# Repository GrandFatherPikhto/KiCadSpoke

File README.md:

# KiCadStamp v1.8.0

**KiCadStamp** is a command‑line **PCB cloning and layout automation** tool for **KiCad 10**, designed as an advanced script‑based alternative to the traditional **KiCad Replicate Layout** plugin. It enables automated **block replication**, component placement, and routing of complex multi‑channel designs using **templates**, **roles**, and the IPC API.

- Moving components (capacitors, resistors, ferrites, crystals, etc.) to specified positions.
- Creating vias and **tracks** attached to the spoke as a whole or to individual components.
- **Cloning** repetitive functional blocks (PI‑filters, DAC channels, power supplies) at different board locations.
- Automatic component selection by **roles** and **nets** – no explicit refdes needed.
- Idempotency: repeated runs never duplicate already‑correctly‑placed items.
- Undo of the last operation.
- Extracting templates from the current selection with net parametrisation and custom origin selection.
- Snapshotting hierarchical channels via a file‑based cloner (`clone-extract`).

---

## Key Features

**An advanced, script‑driven alternative to the classic KiCad Replicate Layout plugin**, built for multi‑channel projects and automated design reuse via the KiCad IPC API.

- **Template‑based approach** – geometry is defined once in local coordinates and reused with arbitrary rotation/translation.
- **Automatic component selection** – roles (`LIGHT`, `HEAVY`, `PI_FILTER_C1`, etc.) replace refdes; components are picked from a pool by net and the `Role` field in the schematic.
- **ClonePlacement** – supports two modes:
  - **by selection** – for one‑off instances (e.g., a single MCU);
  - **by nets** – for repeated blocks, with net name parametrisation via placeholders and `params`. Ambiguity is resolved by physical proximity to the anchor (useful for power filters on common rails). You can also use explicit `refs` as a last resort.
- **Generalised vias and tracks** – all elements (vias, tracks, components) are defined in local coordinates and transformed uniformly (translation, rotation, mirroring).
- **Placement registry** – stores UUIDs of created vias and tracks, ensuring idempotency and automatic cleanup of obsolete entries. Reconciliation is now performed against real elements on the board (via `adapter.get_vias()`/`adapter.get_tracks()`), not only the JSON record, avoiding desynchronisation.
- **Pre‑validation** – checks config before any board modification:
  - existence of templates, pads, and anchor components;
  - component pool sufficiency by roles;
  - uniqueness of clone names and physical anchors (`anchor_ref`, `anchor_role`);
  - correctness of resolved via nets against real board nets;
  - validity of `layer`/`mirror` combinations (mirroring only when layer changes);
  - at most one selection‑based `clone_placement` per run (KiCad allows only one active selection).
- **Diagnostics** – scripts for debugging IPC, geometry, and field reading.
- **File‑based cloner** (`clone-extract`) – parses `.net` and `.kicad_pcb` without IPC, builds a twin map of channels for hierarchical projects.
- **Tracks in templates** – templates can include straight track segments (polylines are supported as a sequence of segments). Track collisions are not automatically checked (rely on KiCad DRC).
- **External template files** – templates can be stored separately as JSON or YAML (wrapped in a `cells:` key) and listed under `include:` in the main config, keeping the main file clean and diff‑friendly.
- **Splitting a profile into subsystem files** – `include:` at the root of a profile merges in one or more other YAML files (each carrying any mix of `extract_profiles`/`clone_placements`/`rules`/`cells`), recursively, with a per‑entry `enabled: false` on the include itself to switch a whole subsystem file off without touching every item inside it (see [docs/config.md](docs/config.md) for merge semantics and duplicate/cycle handling).
- **Scripting API** – `kicadstamp.explore.Board` for ad‑hoc read‑only querying (`board.select(role=..., cluster=..., sheet=..., net=...)`), and `kicadstamp.author` for building `ClonePlacement`/`Rule` in real Python instead of hand‑writing repetitive YAML, either applied directly or dumped back to an `include:`‑ready YAML file (see [docs/python.md](docs/python.md)).

---

## Installation and Dependencies

### Requirements
- Python 3.8 or later.
- KiCad 10.0.4 or later (with IPC API enabled).
- The **kipy** library (Python wrapper for KiCad IPC).

### Installation
```bash
pip install kipy pyyaml sexpdata
```
(For diagnostics, `psutil` may be required.)

### Setting up Roles in the Schematic (Eeschema)
1. Open the symbol in Eeschema.
2. Add a field named **Role** with a value matching the role in the template (e.g., `LIGHT`, `HEAVY`).
3. Run **Update PCB from Schematic** to propagate the field to the board.
4. Verify readability with:
   ```bash
   python -m kicadstamp.diagnostics.test_custom_field C5 --field Role
   ```

---

## Key Concepts

### Why "Spoke"?
In electronics, decoupling/support components (capacitors, pi‑filters) often radiate outward from an
IC's pins, like spokes on a wheel. KiCadStamp automates building this kind of "spoke" topology, letting
you **stamp** it out by rule and role wherever it's needed:
- **Template (`SpokeTemplate`)** – the geometry of one spoke (a capacitor + via + track, or a whole filter block).
- **Spoke (`ManualSpoke`)** – a rule that takes a spoke template and attaches it to a specific pad.
- **Cloning (`ClonePlacement`)** – the next level: takes a template – one spoke or a whole bundle of them
  (e.g. a channel) – and stamps it as an independent unit anywhere on the board, not just on an IC pad.

That maps onto the tool's two names: **Spoke** is the domain shape (the radiating placement pattern),
**Stamp** is the action – the tool that replicates it by rule.

### Template (SpokeTemplate)
A template describes the **local geometry** of one "spoke" – a set of components, vias, and tracks relative to a local origin (0,0) in the `along/across` coordinate system. It contains:
- **`vias`** – vias at the spoke level (usually the power net).
- **`components`** – a list of slots, each with a `role`, local coordinates, angle, and a list of vias (usually to GND).
- **`tracks`** – straight track segments (layer, width, net).

All coordinates are defined **once** at `rotation_deg=0`; when applied, the template is rotated as a whole.

#### Template layer (`layer`)
Each template has an absolute layer (`F.Cu` or `B.Cu`), automatically set during extraction (`extract`). Components on a different layer get an explicit `layer` in their slot.

#### Net parametrisation during extraction
With the `--net-template` option, you can replace literal net names with patterns containing placeholders (e.g., `DAC1_DB1 → DAC{channel}_DB1`) at extraction time. This eliminates manual YAML editing.

### Spoke (ManualSpoke)
Attaches a template to a specific IC pin:
- `pad` – pad number of the target component.
- `shift_x_mm`, `shift_y_mm` – flat shift from the pad centre to the template origin.
- `rotation_deg` – rotation of the entire template.

**Important:** In new config versions, each rule (`rules`) must have its own `anchor_ref`. The global `target_ref` has been removed.

### Roles and Component Pool
Instead of refdes, **roles** are used in the config. For each net (`rule.net`), a pool of components is built, where each component:
- Has a `Role` field with the required value.
- Has at least one pad connected to that net.

Components are sorted in natural numeric order (`C5` < `C10`) and consumed in the order of spokes.

### Cloning (ClonePlacement)
Allows applying a template at an arbitrary point on the board, without tying to IC pads. Supports:
- **Selection mode** – reads roles from the current selection in the PCB editor. You can either omit `nets`/`params` or explicitly set `by_selection: true`. Only one such clone can be processed per run (due to KiCad's single‑selection limitation).
- **Net mode** – for each role, a net is specified (via `nets` or `net_template` with placeholders resolved by `params` and `net_overrides`). If multiple candidates are electrically indistinguishable, the tool can pick the one closest to the anchor (if the distance margin is sufficient). This is useful for power filters on a common rail.
- **Anchor by role** (`anchor_role`) – an alternative to `anchor_ref`: instead of a refdes, you can specify the `Role` field of the anchor component. This survives re‑annotation. You can further narrow the search with `anchor_sheet` (local net prefix) or `anchor_pad`.
- **Explicit refs** (`refs`) – a last‑resort override when candidates are indistinguishable by nets, selection, or proximity.

### Placement Registry (PlacementRegistry + TrackRegistry)
Separate registries for vias and tracks (JSON files next to the config). On subsequent runs:
- already correctly placed items are skipped;
- those that changed position/parameters are deleted and recreated;
- obsolete entries (keys not present in the new plan) are removed (prune).

**Important:** Reconciliation now checks against real elements on the board (`adapter.get_vias()`/`adapter.get_tracks()`), not only the JSON record, preventing desynchronisation due to manual deletions or crashes between registry write and board commit.

### Net Resolution (`net_resolution`)
For cloned templates, net names go through a three‑step resolution:
1. **Literal** – if no placeholders.
2. **Placeholder** – substitution from `params` (e.g., `{channel}` → `2`).
3. **net_overrides** – final override of the resolved name (for hierarchical paths).

During extraction, the reverse operation (`--net-template`) is available, turning literals into patterns.

---

## Configuration File Format (YAML)

Full field-by-field reference for every section (`cells`/`rules`/`clone_placements`/
`thermal_via_arrays`/`points`/`include`/`extract_profiles`) with real, currently-loading examples now
lives in its own page: [docs/config.md](docs/config.md).

---

## CLI Commands

All commands are run via `kicadstamp_cli.py`. If the subcommand is omitted, `apply` is assumed.

### `apply` – apply placement

```bash
python kicadstamp_cli.py apply config.yaml [options]
```

Options:
- `--dry-run` – only show the plan, do not apply changes.
- `--timeout-ms` – IPC timeout in ms (default 20000).
- `--batch-size` – batch size for commits (default 10).
- `--verbose` – verbose output (DEBUG).
- `--log-file` – save logs to a file.
- `--no-collision-check` – disable collision checking.
- `--collision-margin` – margin in mm (default 0.2).
- `--only NAME` – process only the `rules`/`clone_placements`/`thermal_via_arrays` with this name (repeatable); everything else is skipped entirely. `name:` is mandatory on every such entry.

### `extract` – extract template from selection (enhanced)

```bash
python kicadstamp_cli.py extract --name template_name --output config.yaml [--verbose] [--log-file] [--param KEY=VALUE] [--net-template LITERAL=PATTERN] [--origin-by-via-net NET] [--origin-by-component-role ROLE]
```

New options:
- `--param KEY=VALUE` – parameter for `--net-template` verification (e.g., `channel=1`), not written to template.
- `--net-template LITERAL=PATTERN` – replace a real net with a pattern containing placeholders (e.g., `DAC1_DB1=DAC{channel}_DB1`). Can be repeated.
- `--origin-by-via-net NET` – set origin to the position of a via on the specified net (instead of bbox). Fatal if the net is missing or ambiguous.
- `--origin-by-component-role ROLE` – set origin to the position of a component with the specified role.

**Important:** The `--output` extension determines format: `.json` → JSON, otherwise YAML. The file is written wrapped under a `cells:` key, ready to be listed directly under `include:`.

### `undo` – undo the last operation

```bash
python kicadstamp_cli.py undo [--verbose] [--log-file]
```

### `clone-extract` – snapshot a channel (file‑based cloner)

```bash
python kicadstamp_cli.py clone-extract --net project.net --pcb project.kicad_pcb --channel Channel_0 --output snapshot.yaml [--verbose]
```

---

## Usage Examples

### 1. Standard run
```bash
python kicadstamp_cli.py 10CL006YE144C8G.yaml
```

### 2. Dry run
```bash
python kicadstamp_cli.py config.yaml --dry-run
```

### 3. Process a single clone (selection mode)
```bash
python kicadstamp_cli.py config.yaml --only pi_filter_vccio
```

### 4. Extract a template with parametrisation and origin by via
Select the elements on the board, then:
```bash
python kicadstamp_cli.py extract --name my_filter --output my_filter.json --net-template "DAC1_DB1=DAC{channel}_DB1" --param channel=1 --origin-by-via-net "/Channel_0/DAC/+3V3_CLKVDD" --verbose
```

### 5. Undo
```bash
python kicadstamp_cli.py undo --verbose
```

---

## Diagnostics and Known Issues

### KiCad Bug #24966 (crash on first write via IPC)
When the Schematic Editor is open, the session's first `begin_commit()`/`push_commit()` transaction (even a
no-op one) can crash KiCad (null pointer in `API_HANDLER_EDITOR::checkForBusy`).

**Symptoms:** KiCad silently closes, client gets `ConnectionError: Error receiving reply from KiCad: Timed out`.

**Workaround:** close the schematic editor before running `apply`. The tool includes a warning and retries,
but the crash remains a KiCad defect. In practice it's specifically the *session's first* write that's
vulnerable — if the first `apply` run is done with only the PCB Editor open, opening the Schematic Editor
afterwards is usually safe. Full write-up, a related bug (#24970), and the full crash-hunting toolkit —
see [docs/crash_hunting.md](./docs/crash_hunting.md).

### Diagnostic scripts
`kicadstamp/diagnostics/` includes:
- `diagnose_first_write_crash.py` – reproduces the crash ladder, see [docs/diagnose_first_write_crash.md](./docs/diagnose_first_write_crash.md).
- `test_custom_fields.py` – checks `Role` field reading.
- `test_move_one_cap.py`, `test_flip_one_cap.py`, `test_create_one_via.py`, `test_pad_mirror_convention.py`, `get_selected_component.py`, `get_pad_bbox.py`, `diagnostic_keepout.py`.

---

## Project Structure (brief)

```
kicadstamp/
├── __init__.py
├── kicadstamp_cli.py          # CLI entry point
├── apply_pipeline.py          # cmd_apply and ApplyPipeline class
├── cli_extract.py             # cmd_extract command logic
├── logging_setup.py           # Logging configuration
├── runtime_context.py         # RuntimeContext dataclass
├── sheet_names.py             # Sheet UUID → name resolution
├── i18n.py                    # gettext internationalisation
├── author.py                  # Scripting: dump/apply helpers (explore/author)
├── explore.py                 # Board query helpers
├── config/                    # Configuration package (loader.py, models.py, includes.py)
├── constants.py               # Global constants (ROLE_FIELD_NAME, tolerances, etc.)
├── exceptions.py              # Exception hierarchy
├── validation.py              # Pre‑checks (nets, uniqueness, selection mode, layer/mirror)
├── registry.py                # Via and track registries (reconcile with live elements)
├── net_resolution.py          # Net resolution with placeholders for ClonePlacement
├── template_extraction.py     # Extract with parametrisation and custom origin
├── undo.py                    # Undo last placement operation
├── geometry/                  # Spoke_layout, keepout, thermal_grid, pad_projection, clone_geometry
├── kicad/                     # KiCad IPC adapter and IBoardAdapter interface
├── placement/                 # Planner, executors, services
│   ├── services/              # component_pool, clone_role_resolver, position_tracker, component_resolver, etc.
├── cloner/                    # File‑based cloner (extract, netlist, pcb, models, sexp)
├── diagnostics/               # Diagnostic scripts
├── utils/                     # Utilities
│   └── units.py               # MM = 1_000_000 constant
└── tests/                     # Unit and integration tests
```

---

## 📚 Technical Documentation

Detailed documentation is in the `docs/` folder:

- [Project architecture](./docs/architect.md)
- [CLI commands](./docs/commands.md)
- [Geometry utilities](./docs/geometry.md)
- [KiCad adapter](./docs/kicad.md)
- [Using kipy](./docs/kipy.md)
- [Placement planning and execution](./docs/placement.md)
- [YAML configuration reference](./docs/config.md)
- [Coding placement in Python: explore/author](./docs/python.md)
- [PyQt6 GUI](./docs/gui.md)
- [fieldstool: bulk Role/Cluster set/rename in .kicad_sch](./docs/fieldstool.md)
- [Tests](./docs/tests.md)
- [Top‑level modules](./docs/uplevel_modules.md)
- [File‑based cloner](./docs/cloner.md)
- [Diagnostics](./docs/diagnostics.md)
- [KiCad crash hunting toolkit (#24966 / #24970)](./docs/crash_hunting.md)
- [`diagnose_first_write_crash.py` reference](./docs/diagnose_first_write_crash.md)
- [Internationalization (i18n) — gettext/Babel](./docs/i18n.md)
- [Template rotation and transformation](./docs/rotate_template.md)
- [Module dependency diagram](./docs/diagram.md)

---

## Versioning

Single source of truth: `__version__` in [`kicadstamp/__init__.py`](./kicadstamp/__init__.py) — this README's
header and `kicadstamp_cli.py --version`/`-V` both read it, not a separate literal. Versioned by
session/stage, not by commit: MINOR bumps once per notable block of work (e.g. one architecture‑refactor
session, regardless of how many commits it took), PATCH for point fixes made between stages, MAJOR
reserved for actual breaking changes to the CLI or YAML config format.

---

## License

This project is distributed under the **MIT** license. See the `LICENSE` file for details.

---

**KiCadStamp** is not just a utility – it's a modern alternative to manual block copying in KiCad.

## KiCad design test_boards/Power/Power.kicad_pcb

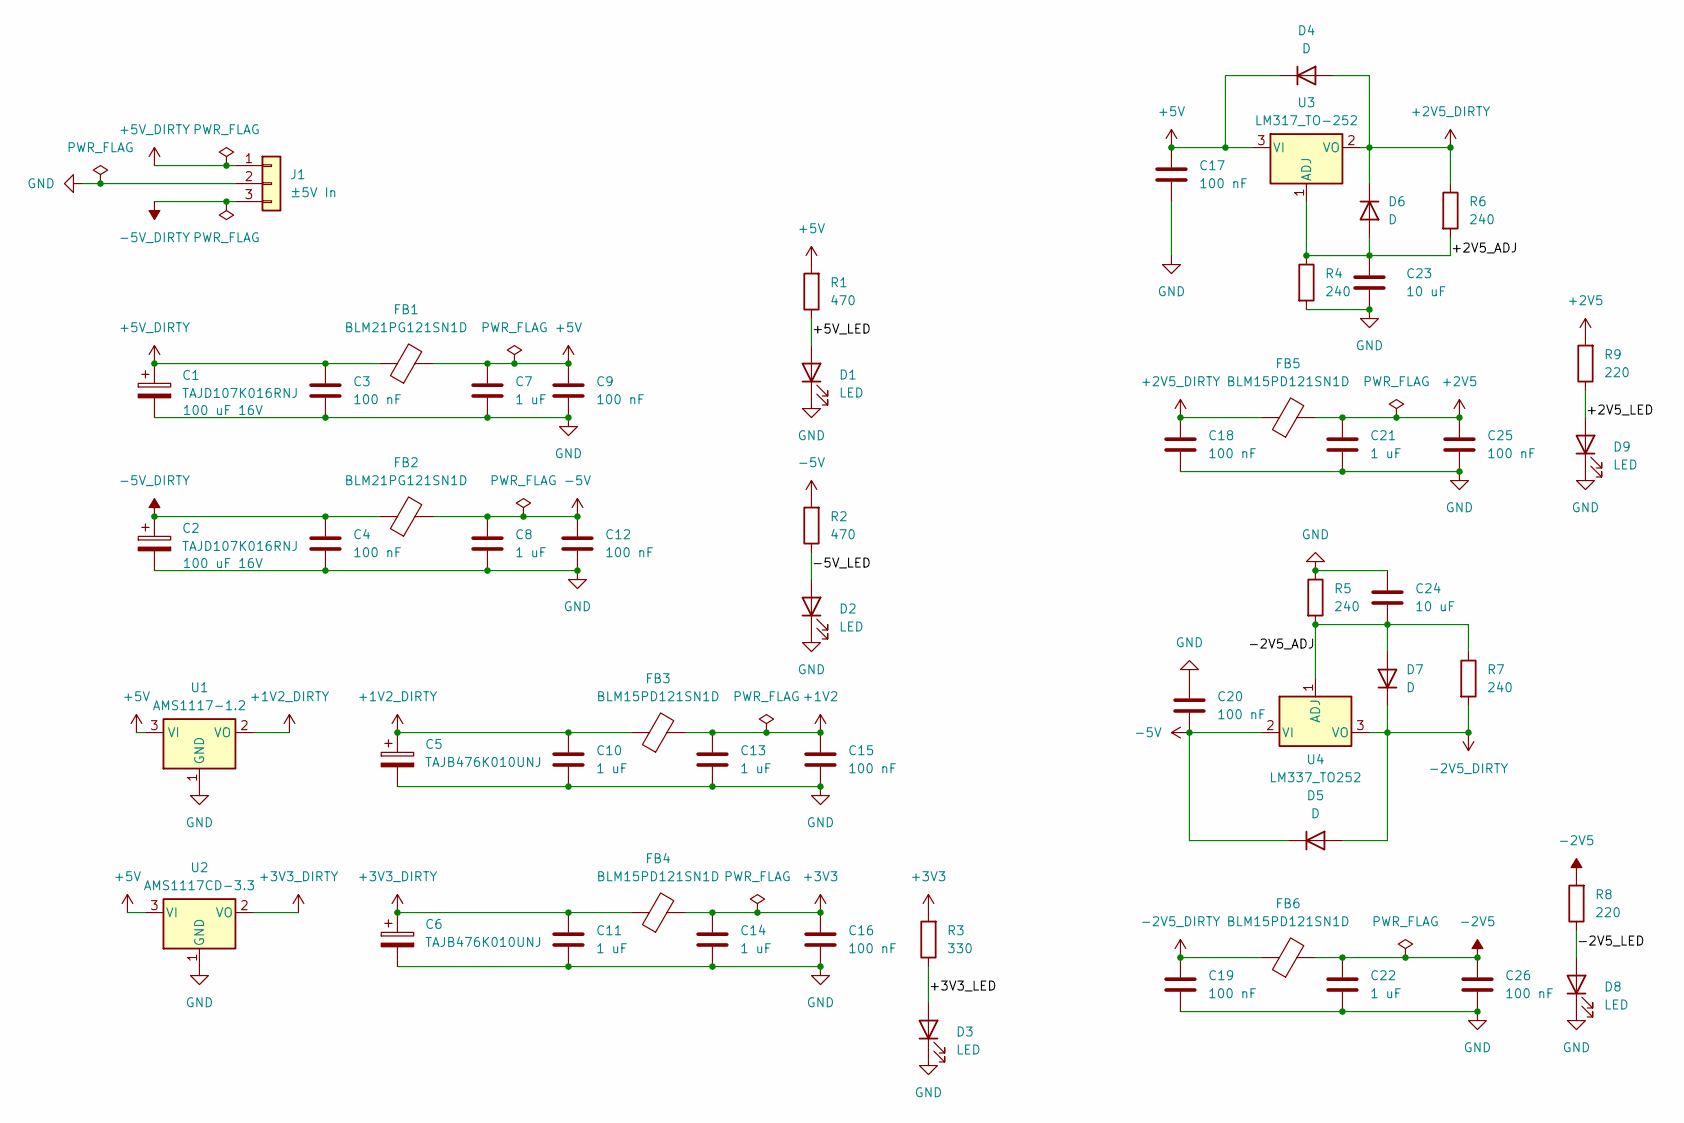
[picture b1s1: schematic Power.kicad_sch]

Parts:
C1, C2: TAJD107K016RNJ; CP_EIA-7343-20_Kemet-V_HandSolder
C3, C4, C9, C12, C15, C16, C17, C18, C19, C20, C25, C26: 100 nF; C_0603_1608Metric_Pad1.08x0.95mm_HandSolder
C5, C6: TAJB476K010UNJ; CP_EIA-3528-12_Kemet-T_HandSolder
C7, C8: 1 uF; C_1206_3216Metric_Pad1.33x1.80mm_HandSolder
C10, C11, C13, C14, C21, C22: 1 uF; C_0603_1608Metric_Pad1.08x0.95mm_HandSolder
C23, C24: 10 uF; C_0805_2012Metric_Pad1.18x1.45mm_HandSolder
D1, D2, D3, D8, D9: LED; D_0805_2012Metric_Pad1.15x1.40mm_HandSolder
D4, D5, D6, D7: D; D_SMA_Handsoldering
FB1, FB2: BLM21PG121SN1D; L_0805_2012Metric
FB3, FB4, FB5, FB6: BLM15PD121SN1D; L_0402_1005Metric
J1: ±5V In; JST_XH_B3B-XH-A_1x03_P2.50mm_Vertical
R1, R2: 470; R_0603_1608Metric_Pad0.98x0.95mm_HandSolder
R3: 330; R_0603_1608Metric_Pad0.98x0.95mm_HandSolder
R4, R5, R6, R7: 240; R_0603_1608Metric_Pad0.98x0.95mm_HandSolder
R8, R9: 220; R_0603_1608Metric_Pad0.98x0.95mm_HandSolder
U1: AMS1117-1.2; SOT-223-3_TabPin2
U2: AMS1117CD-3.3; TO-252-3_TabPin2
U3: LM317_TO-252; TO-252-2
U4: LM337_TO252; TO-252-2

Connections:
+1V2: C13.1, C15.1, FB3.2
+1V2_DIRTY: C5.1, C10.1, FB3.1, U1.2 (VO)
+2V5: C21.1, C25.1, FB5.2, R9.2
+2V5_DIRTY: C18.1, D4.2 (A), D6.1 (K), FB5.1, R6.1, U3.2 (VO)
+3V3: C14.1, C16.1, FB4.2, R3.2
+3V3_DIRTY: C6.1, C11.1, FB4.1, U2.2 (VO)
+5V: C7.1, C9.1, C17.2, D4.1 (K), FB1.2, R1.2, U1.3 (VI), U2.3 (VI), U3.3 (VI)
+5V_DIRTY: C1.1, C3.1, FB1.1, J1.1
-2V5: C22.1, C26.1, FB6.2, R8.2
-2V5_DIRTY: C19.1, D5.2 (A), D7.1 (K), FB6.1, R7.2, U4.3 (VO)
-5V: C8.1, C12.1, C20.1, D5.1 (K), FB2.2, R2.2, U4.2 (VI)
-5V_DIRTY: C2.1, C4.1, FB2.1, J1.3
/+2V5_ADJ: C23.1, D6.2 (A), R4.1, R6.2, U3.1 (ADJ)
/+2V5_LED: D9.2 (A), R9.1
/+3V3_LED: D3.2 (A), R3.1
/+5V_LED: D1.2 (A), R1.1
/-2V5_ADJ: C24.2, D7.2 (A), R5.2, R7.1, U4.1 (ADJ)
/-2V5_LED: D8.2 (A), R8.1
/-5V_LED: D2.2 (A), R2.1
GND: C1.2, C2.2, C3.2, C4.2, C5.2, C6.2, C7.2, C8.2, C9.2, C10.2, C11.2, C12.2, C13.2, C14.2, C15.2, C16.2, C17.1, C18.2, C19.2, C20.2, C21.2, C22.2, C23.2, C24.1, C25.2, C26.2, D1.1 (K), D2.1 (K), D3.1 (K), D8.1 (K), D9.1 (K), J1.2, R4.2, R5.1, U1.1 (GND), U2.1 (GND)

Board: 4 copper layers, 55 parts (0 on the bottom side), 20 nets, no tracks yet.

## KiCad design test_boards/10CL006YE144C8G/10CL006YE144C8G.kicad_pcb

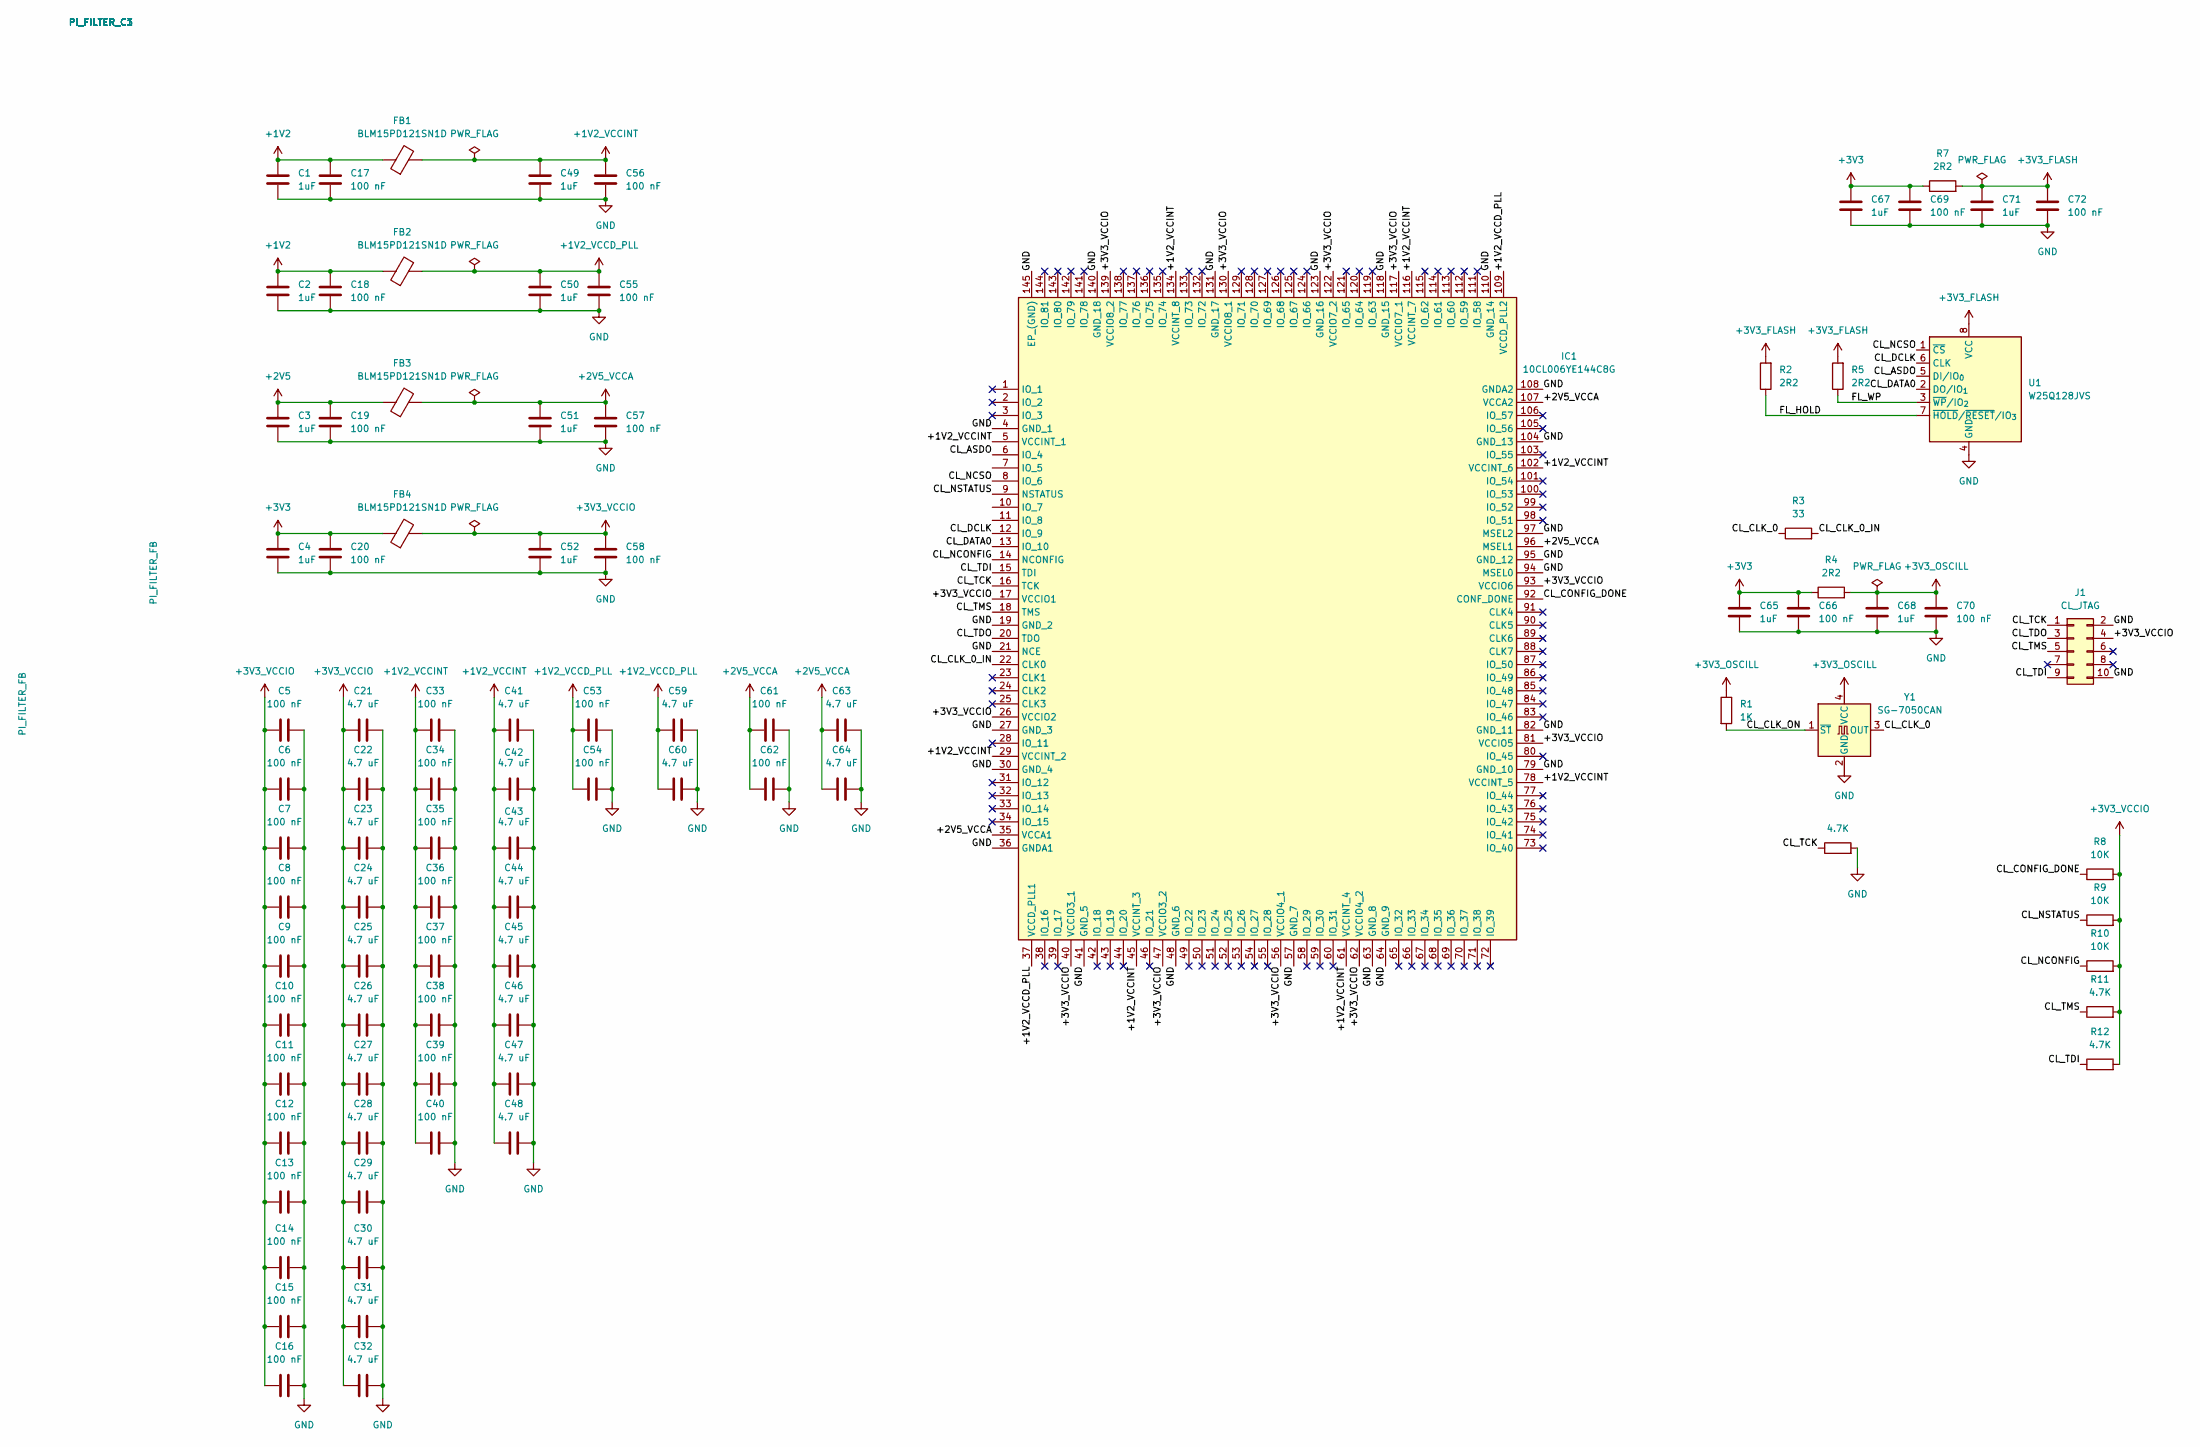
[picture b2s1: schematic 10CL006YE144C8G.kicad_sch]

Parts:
C1, C2, C3, C4, C49, C50, C51, C52, C65, C67, C68, C71: 1uF; C_0603_1608Metric_Pad1.08x0.95mm_HandSolder
C5, C6, C7, C8, C9, C10, C11, C12, C13, C14, C15, C16, C17, C18, C19, C20, C33, C34, C35, C36, C37, C38, C39, C40, C53, C54, C55, C56, C57, C58, C61, C62, C66, C69, C70, C72: 100 nF; C_0402_1005Metric_Pad0.74x0.62mm_HandSolder
C21, C22, C23, C24, C25, C26, C27, C28, C29, C30, C31, C32, C41, C42, C43, C44, C45, C46, C47, C48, C59, C60, C63, C64: 4.7 uF; C_0603_1608Metric_Pad1.08x0.95mm_HandSolder
FB1, FB2, FB3, FB4: BLM15PD121SN1D; L_0402_1005Metric
IC1: 10CL006YE144C8G; QFP50P2200X2200X165-145N; Manufacturer_Part_Number 10CL006YE144C8G; Mouser Part Number 989-10CL006YE144C8G
J1: CL_JTAG; IDC-Header_2x05_P2.54mm_Vertical
R1: 1K; R_0402_1005Metric_Pad0.72x0.64mm_HandSolder
R2, R4, R5, R7: 2R2; R_0402_1005Metric_Pad0.72x0.64mm_HandSolder
R3: 33; R_0402_1005Metric_Pad0.72x0.64mm_HandSolder
R6, R11, R12: 4.7K; R_0402_1005Metric_Pad0.72x0.64mm_HandSolder
R8, R9, R10: 10K; R_0402_1005Metric_Pad0.72x0.64mm_HandSolder
U1: W25Q128JVS; SOIC-8_5.3x5.3mm_P1.27mm
Y1: SG-7050CAN; Oscillator_SMD_SeikoEpson_SG8002CA-4Pin_7.0x5.0mm

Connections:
+1V2: C1.1, C2.1, C17.1, C18.1, FB1.1, FB2.1
+1V2_VCCD_PLL: C50.1, C53.1, C54.1, C55.1, C59.1, C60.1, FB2.2, IC1.37 (VCCD_PLL1), IC1.109 (VCCD_PLL2)
+1V2_VCCINT: C33.1, C34.1, C35.1, C36.1, C37.1, C38.1, C39.1, C40.1, C41.1, C42.1, C43.1, C44.1, C45.1, C46.1, C47.1, C48.1, C49.1, C56.1, FB1.2, IC1.5 (VCCINT_1), IC1.29 (VCCINT_2), IC1.45 (VCCINT_3), IC1.61 (VCCINT_4), IC1.78 (VCCINT_5), IC1.102 (VCCINT_6), IC1.116 (VCCINT_7), IC1.134 (VCCINT_8)
+2V5: C3.1, C19.1, FB3.1
+2V5_VCCA: C51.1, C57.1, C61.1, C62.1, C63.1, C64.1, FB3.2, IC1.35 (VCCA1), IC1.96 (MSEL1), IC1.107 (VCCA2)
+3V3: C4.1, C20.1, C65.1, C66.1, C67.1, C69.1, FB4.1, R4.1, R7.1
+3V3_FLASH: C71.1, C72.2, R2.2, R5.2, R7.2, U1.8 (VCC)
+3V3_OSCILL: C68.1, C70.2, R1.1, R4.2, Y1.4 (VCC)
+3V3_VCCIO: C5.1, C6.1, C7.1, C8.1, C9.1, C10.1, C11.1, C12.1, C13.1, C14.1, C15.1, C16.1, C21.1, C22.1, C23.1, C24.1, C25.1, C26.1, C27.1, C28.1, C29.1, C30.1, C31.1, C32.1, C52.1, C58.1, FB4.2, IC1.17 (VCCIO1), IC1.26 (VCCIO2), IC1.40 (VCCIO3_1), IC1.47 (VCCIO3_2), IC1.56 (VCCIO4_1), IC1.62 (VCCIO4_2), IC1.81 (VCCIO5), IC1.93 (VCCIO6), IC1.117 (VCCIO7_1), IC1.122 (VCCIO7_2), IC1.130 (VCCIO8_1), IC1.139 (VCCIO8_2), J1.4, R8.2, R9.2, R10.2, R11.2, R12.2
/CL_ASDO: IC1.6 (IO_4), U1.5 (DI/IO_{0})
/CL_CLK_0: R3.1, Y1.3 (OUT)
/CL_CLK_0_IN: IC1.22 (CLK0), R3.2
/CL_CLK_ON: R1.2, Y1.1 (~ST)
/CL_CONFIG_DONE: IC1.92 (CONF_DONE), R8.1
/CL_DATA0: IC1.13 (IO_10), U1.2 (DO/IO_{1})
/CL_DCLK: IC1.12 (IO_9), U1.6 (CLK)
/CL_NCONFIG: IC1.14 (NCONFIG), R10.1
/CL_NCSO: IC1.8 (IO_6), U1.1 (~CS)
/CL_NSTATUS: IC1.9 (NSTATUS), R9.1
/CL_TCK: IC1.16 (TCK), J1.1, R6.1
/CL_TDI: IC1.15 (TDI), J1.9, R12.1
/CL_TDO: IC1.20 (TDO), J1.3
/CL_TMS: IC1.18 (TMS), J1.5, R11.1
/FL_HOLD: R2.1, U1.7 (~HOLD/~RESET/IO_{3})
/FL_WP: R5.1, U1.3 (~WP/IO_{2})
GND: C1.2, C2.2, C3.2, C4.2, C5.2, C6.2, C7.2, C8.2, C9.2, C10.2, C11.2, C12.2, C13.2, C14.2, C15.2, C16.2, C17.2, C18.2, C19.2, C20.2, C21.2, C22.2, C23.2, C24.2, C25.2, C26.2, C27.2, C28.2, C29.2, C30.2, C31.2, C32.2, C33.2, C34.2, C35.2, C36.2, C37.2, C38.2, C39.2, C40.2, C41.2, C42.2, C43.2, C44.2, C45.2, C46.2, C47.2, C48.2, C49.2, C50.2, C51.2, C52.2, C53.2, C54.2, C55.2, C56.2, C57.2, C58.2, C59.2, C60.2, C61.2, C62.2, C63.2, C64.2, C65.2, C66.2, C67.2, C68.2, C69.2, C70.1, C71.2, C72.1, IC1.4 (GND_1), IC1.19 (GND_2), IC1.21 (NCE), IC1.27 (GND_3), IC1.30 (GND_4), IC1.36 (GNDA1), IC1.41 (GND_5), IC1.48 (GND_6), IC1.57 (GND_7), IC1.63 (GND_8), IC1.64 (GND_9), IC1.79 (GND_10), IC1.82 (GND_11), IC1.94 (MSEL0), IC1.95 (GND_12), IC1.97 (MSEL2), IC1.104 (GND_13), IC1.108 (GNDA2), IC1.110 (GND_14), IC1.118 (GND_15), IC1.123 (GND_16), IC1.131 (GND_17), IC1.140 (GND_18), IC1.145 (EP_(GND)), J1.2, J1.10, R6.2, U1.4 (GND), Y1.2 (GND)

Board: 2 copper layers, 92 parts (0 on the bottom side), 26 nets, no tracks yet.

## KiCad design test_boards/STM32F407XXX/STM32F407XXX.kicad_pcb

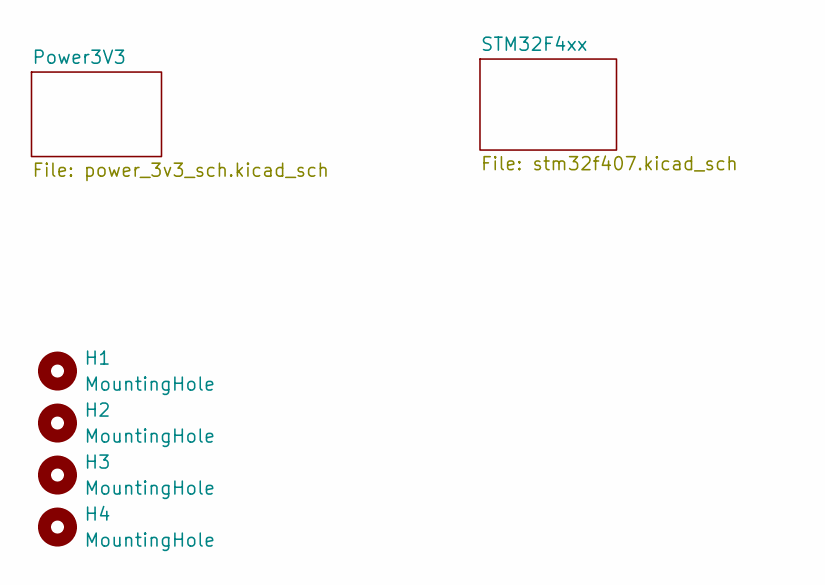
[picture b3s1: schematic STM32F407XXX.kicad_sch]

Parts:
H1, H2, H3, H4: MountingHole; MountingHole_3.2mm_M3

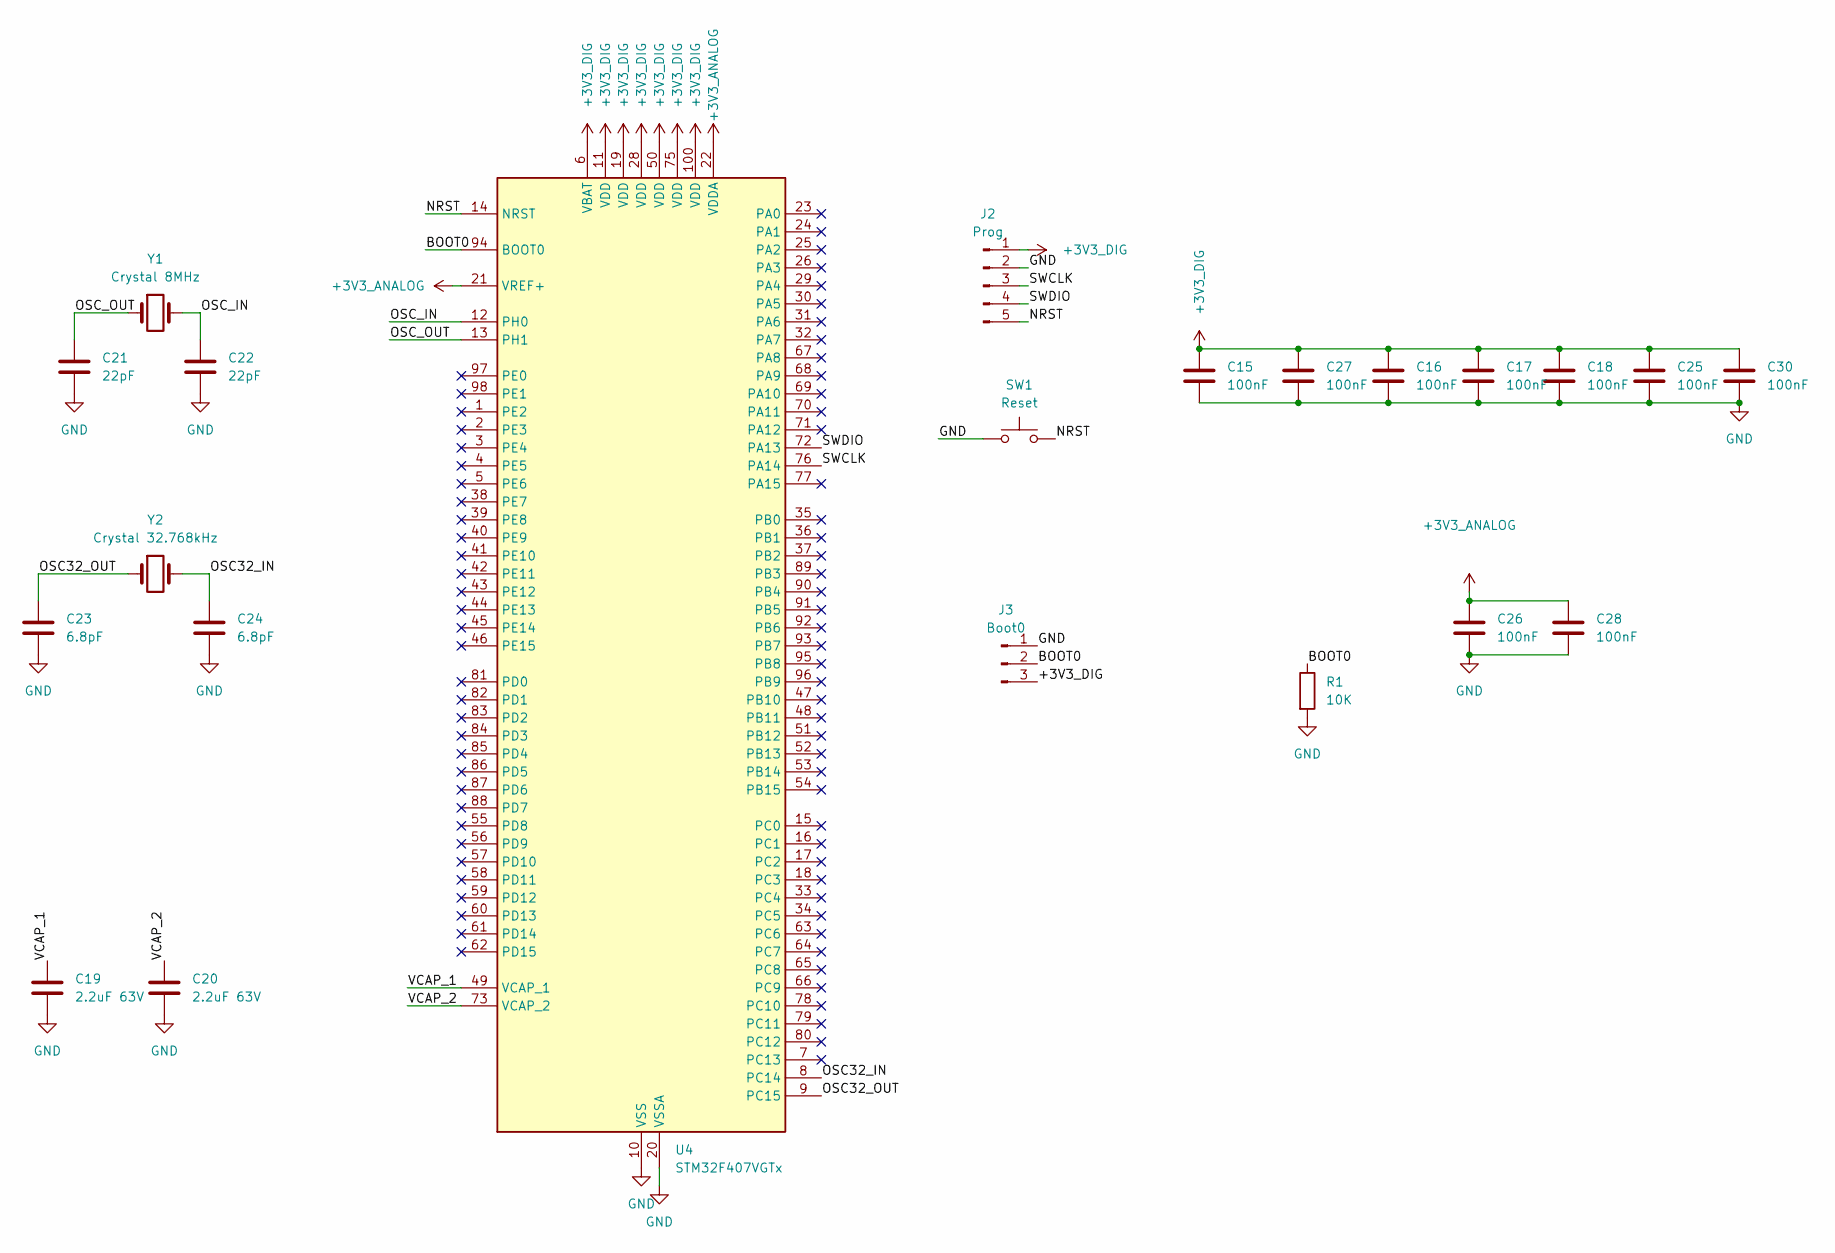
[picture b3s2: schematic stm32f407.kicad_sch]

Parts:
C15, C16, C17, C18, C25, C26, C27, C28, C30: 100nF; C_0603_1608Metric_Pad1.08x0.95mm_HandSolder
C19, C20: 2.2uF 63V; C_1210_3225Metric_Pad1.33x2.70mm_HandSolder
C21, C22: 22pF; C_0402_1005Metric_Pad0.74x0.62mm_HandSolder
C23, C24: 6.8pF; C_0402_1005Metric_Pad0.74x0.62mm_HandSolder
J2: Prog; PinHeader_1x05_P2.54mm_Vertical
J3: Boot0; PinHeader_1x03_P2.54mm_Vertical
R1: 10K; R_0603_1608Metric_Pad0.98x0.95mm_HandSolder
SW1: Reset; SW_PUSH_6mm
U4: STM32F407VGTx; LQFP-100_14x14mm_P0.5mm
Y1: Crystal 8MHz; Crystal_HC49-4H_Vertical
Y2: Crystal 32.768kHz; Crystal_HC49-4H_Vertical

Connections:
+3V3_ANALOG: C26.1, C28.1, U4.21 (VREF+), U4.22 (VDDA); also elsewhere on the board
+3V3_DIG: C15.1, C16.1, C17.1, C18.1, C25.1, C27.1, C30.1, J2.1, J3.3, U4.6 (VBAT), U4.11 (VDD), U4.19 (VDD), U4.28 (VDD), U4.50 (VDD), U4.75 (VDD), U4.100 (VDD); also elsewhere on the board
/STM32F4xx/BOOT0: J3.2, R1.1, U4.94 (BOOT0)
/STM32F4xx/NRST: J2.5, SW1.2, U4.14 (NRST)
/STM32F4xx/OSC32_IN: C24.1, U4.8 (PC14), Y2.2
/STM32F4xx/OSC32_OUT: C23.1, U4.9 (PC15), Y2.1
/STM32F4xx/OSC_IN: C22.1, U4.12 (PH0), Y1.2
/STM32F4xx/OSC_OUT: C21.1, U4.13 (PH1), Y1.1
/STM32F4xx/SWCLK: J2.3, U4.76 (PA14)
/STM32F4xx/SWDIO: J2.4, U4.72 (PA13)
/STM32F4xx/VCAP_1: C19.1, U4.49 (VCAP_1)
/STM32F4xx/VCAP_2: C20.1, U4.73 (VCAP_2)
GND: C15.2, C16.2, C17.2, C18.2, C19.2, C20.2, C21.2, C22.2, C23.2, C24.2, C25.2, C26.2, C27.2, C28.2, C30.2, J2.2, J3.1, R1.2, SW1.1, U4.10 (VSS), U4.20 (VSSA), U4.27 (VSS), U4.74 (VSS), U4.99 (VSS); also elsewhere on the board

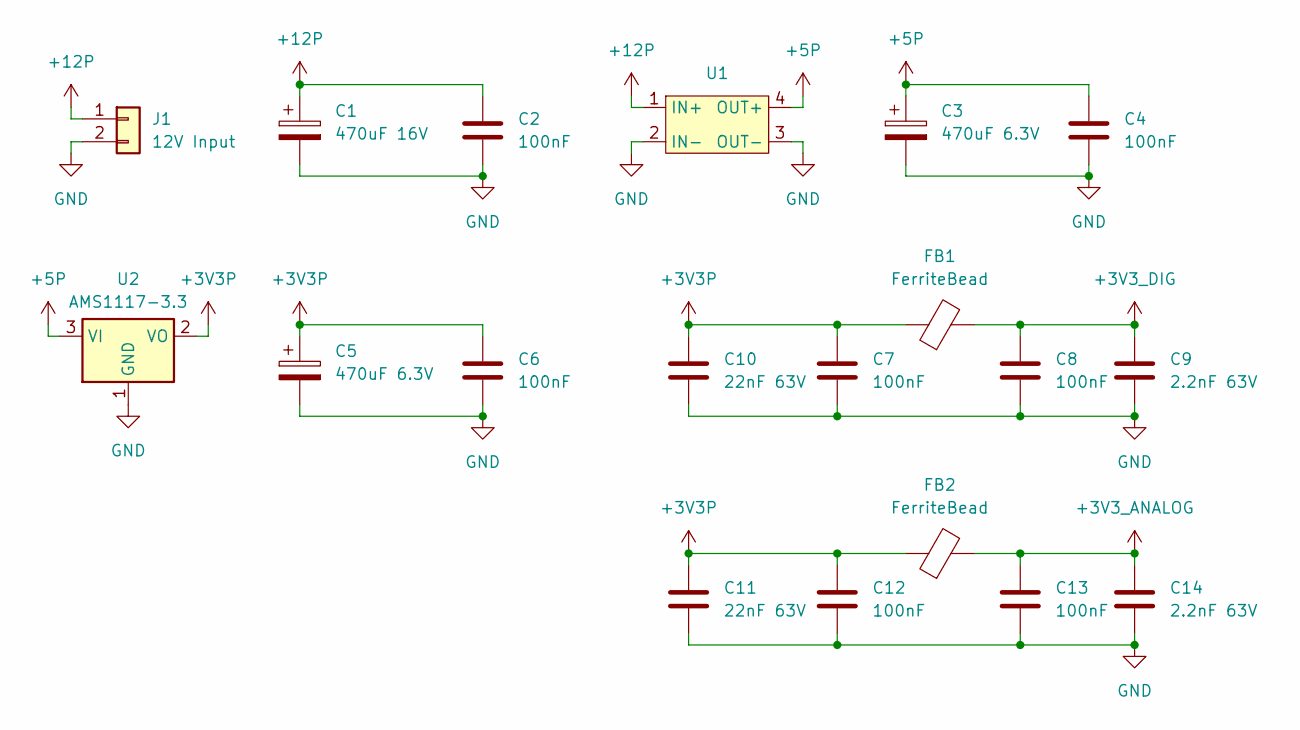
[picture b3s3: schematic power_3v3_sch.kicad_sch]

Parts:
C1: 470uF 16V; CP_Radial_D10.0mm_P5.00mm
C2, C4, C6, C7, C8, C12, C13: 100nF; C_0603_1608Metric_Pad1.08x0.95mm_HandSolder
C3, C5: 470uF 6.3V; CP_EIA-7343-31_Kemet-D_HandSolder
C9, C14: 2.2nF 63V; C_0402_1005Metric_Pad0.74x0.62mm_HandSolder
C10, C11: 22nF 63V; C_0402_1005Metric_Pad0.74x0.62mm_HandSolder
FB1, FB2: FerriteBead; L_0603_1608Metric_Pad1.05x0.95mm_HandSolder
J1: 12V Input; JST_XH_B2B-XH-AM_1x02_P2.50mm_Vertical
U1: Converter_DC-DC_Mini360
U2: AMS1117-3.3; SOT-223-3_TabPin2

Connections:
+3V3P: C5.1, C6.1, C7.1, C10.1, C11.1, C12.1, FB1.1, FB2.1, U2.2 (VO)
+3V3_ANALOG: C13.1, C14.1, FB2.2; also elsewhere on the board
+3V3_DIG: C8.1, C9.1, FB1.2; also elsewhere on the board
+5P: C3.1, C4.1, U1.4 (OUT+), U2.3 (VI)
+12P: C1.1, C2.1, J1.1, U1.1 (IN+)
GND: C1.2, C2.2, C3.2, C4.2, C5.2, C6.2, C7.2, C8.2, C9.2, C10.2, C11.2, C12.2, C13.2, C14.2, J1.2, U1.2 (IN-), U1.3 (OUT-), U2.1 (GND); also elsewhere on the board

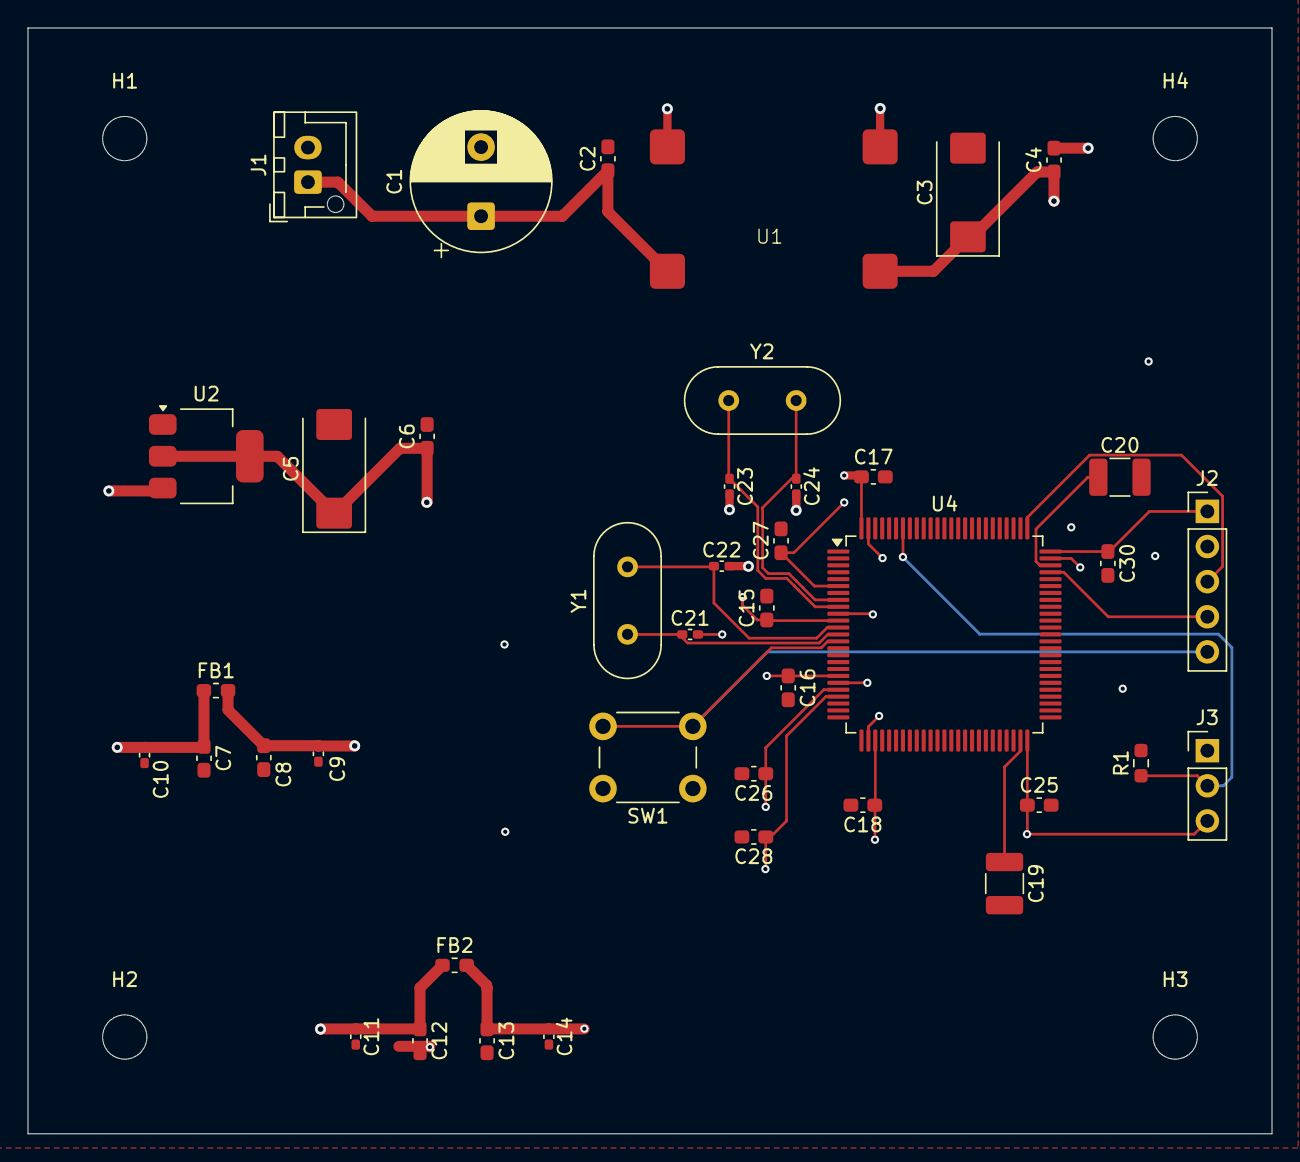
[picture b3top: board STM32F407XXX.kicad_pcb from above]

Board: 4 copper layers, 90.0 x 80.0 mm, 45 parts (0 on the bottom side), 16 nets.

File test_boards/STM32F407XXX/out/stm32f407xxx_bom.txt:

=== BOM (Список компонентов) для stm32f407xxx.net ===

Компонент    | Номинал                   | Корпус (Footprint)            
-------------------------------------------------------------------------
C1           | 470uF 16V                 | CP_Radial_D10.0mm_P5.00mm     
C2           | 100nF                     | C_0603_1608Metric_Pad1.08x0.95mm_HandSolder
C3           | 470uF 6.3V                | CP_EIA-7343-31_Kemet-D_HandSolder
C4           | 100nF                     | C_0603_1608Metric_Pad1.08x0.95mm_HandSolder
C5           | 470uF 6.3V                | CP_EIA-7343-31_Kemet-D_HandSolder
C6           | 100nF                     | C_0603_1608Metric_Pad1.08x0.95mm_HandSolder
C7           | 100nF                     | C_0603_1608Metric_Pad1.08x0.95mm_HandSolder
C8           | 100nF                     | C_0603_1608Metric_Pad1.08x0.95mm_HandSolder
C9           | 2.2nF 63V                 | C_1210_3225Metric_Pad1.33x2.70mm_HandSolder
C10          | 22nF 63V                  | C_1210_3225Metric_Pad1.33x2.70mm_HandSolder
C11          | 22nF 63V                  | C_1210_3225Metric_Pad1.33x2.70mm_HandSolder
C12          | 100nF                     | C_0603_1608Metric_Pad1.08x0.95mm_HandSolder
C13          | 100nF                     | C_0603_1608Metric_Pad1.08x0.95mm_HandSolder
C14          | 2.2nF 63V                 | C_1210_3225Metric_Pad1.33x2.70mm_HandSolder
C15          | 100nF                     | C_0603_1608Metric_Pad1.08x0.95mm_HandSolder
C16          | 100nF                     | C_0603_1608Metric_Pad1.08x0.95mm_HandSolder
C17          | 100nF                     | C_0603_1608Metric_Pad1.08x0.95mm_HandSolder
C18          | 100nF                     | C_0603_1608Metric_Pad1.08x0.95mm_HandSolder
C19          | 2.2uF 63V                 | C_1210_3225Metric_Pad1.33x2.70mm_HandSolder
C20          | 2.2uF 63V                 | C_1210_3225Metric_Pad1.33x2.70mm_HandSolder
C21          | 22pF                      | C_0402_1005Metric_Pad0.74x0.62mm_HandSolder
C22          | 22pF                      | C_0402_1005Metric_Pad0.74x0.62mm_HandSolder
C23          | 6.8pF                     | C_0402_1005Metric_Pad0.74x0.62mm_HandSolder
C24          | 6.8pF                     | C_0402_1005Metric_Pad0.74x0.62mm_HandSolder
C25          | 100nF                     | C_0603_1608Metric_Pad1.08x0.95mm_HandSolder
C26          | 100nF                     | C_0603_1608Metric_Pad1.08x0.95mm_HandSolder
C30          | 100nF                     | C_0603_1608Metric_Pad1.08x0.95mm_HandSolder
FB1          | FerriteBead               | L_0603_1608Metric_Pad1.05x0.95mm_HandSolder
FB2          | FerriteBead               | L_0603_1608Metric_Pad1.05x0.95mm_HandSolder
J1           | 12V Input                 | JST_XH_B2B-XH-AM_1x02_P2.50mm_Vertical
J2           | Prog                      | PinHeader_1x05_P2.54mm_Vertical
J3           | Boot0                     | PinHeader_1x03_P2.54mm_Vertical
R1           | 10K                       | R_0603_1608Metric_Pad0.98x0.95mm_HandSolder
SW1          | Reset                     | SW_PUSH_6mm                   
U1           | ~                         | Converter_DC-DC_Mini360       
U2           | AMS1117-3.3               | SOT-223-3_TabPin2             
U4           | STM32F407VGTx             | LQFP-100_14x14mm_P0.5mm       
Y1           | Crystal 8MHz              | Crystal_HC49-4H_Vertical      
Y2           | Crystal 32.768kHz         | Crystal_HC49-4H_Vertical
